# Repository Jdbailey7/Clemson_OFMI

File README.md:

# Clemson OFMI
This repository houses the hardware and software for the Optical Fiber Michelson
Interrogator (OFMI) designed for geophysical applications by Dr. Scott DeWolf.
Scott is an assistant research professor at Clemson University.

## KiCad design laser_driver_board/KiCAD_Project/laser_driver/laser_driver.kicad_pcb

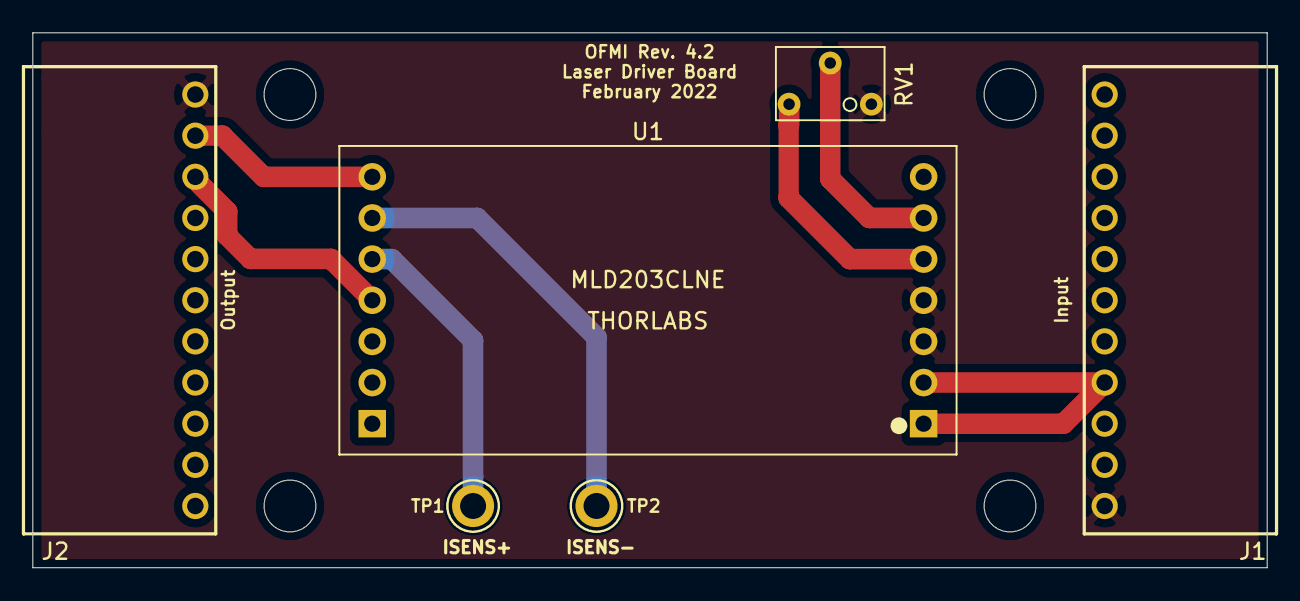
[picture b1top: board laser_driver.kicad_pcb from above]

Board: 2 copper layers, 76.2 x 33.0 mm, 11 parts (0 on the bottom side), 8 nets.

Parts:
H1, H2, H3, H4: MountingHole; MountingHole_3.2mm_M3_DIN965
J1: Input; SAMTEC-TSW-111-08-X-S-RA
J2: Output; SAMTEC-TSW-111-08-X-S-RA
PCB1: barepcb
RV1: 100k; 3266W
TP1, TP2: TestPoint; 5006_TestPoint
U1: MLD203CLNE; MLD203CLN

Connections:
+5V: J1.4, U1.1, U1.2
/ISENS+: TP1.1, U1.12
/ISENS-: TP2.1, U1.13
/ISET: RV1.2, U1.6
/LDA: J2.2, U1.14
/LDC: J2.3, U1.11
GND: J1.1, J2.1, RV1.1, U1.3, U1.4
unnamed: RV1.3, U1.5

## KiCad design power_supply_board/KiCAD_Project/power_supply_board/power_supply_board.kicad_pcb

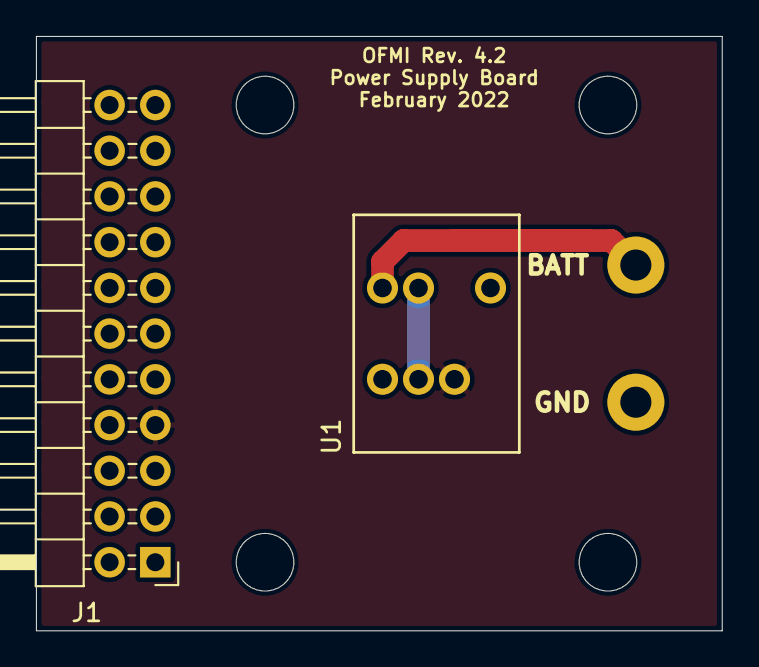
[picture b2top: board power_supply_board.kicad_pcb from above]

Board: 2 copper layers, 38.1 x 33.0 mm, 8 parts (0 on the bottom side), 3 nets.

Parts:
H1, H2, H3, H4: MountingHole; MountingHole_3.2mm_M3_DIN965
J1: To Digitiziers; Pin_Header_Angled_2x11_Pitch2.54mm
J2: Power Input; 16AWG
PCB1: barepcb
U1: TDN 5-2411WI; TDN5WI

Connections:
+5V: J1.7, U1.7
+BATT: J2.2, U1.1
GND: J1.1, J2.1, U1.2, U1.6

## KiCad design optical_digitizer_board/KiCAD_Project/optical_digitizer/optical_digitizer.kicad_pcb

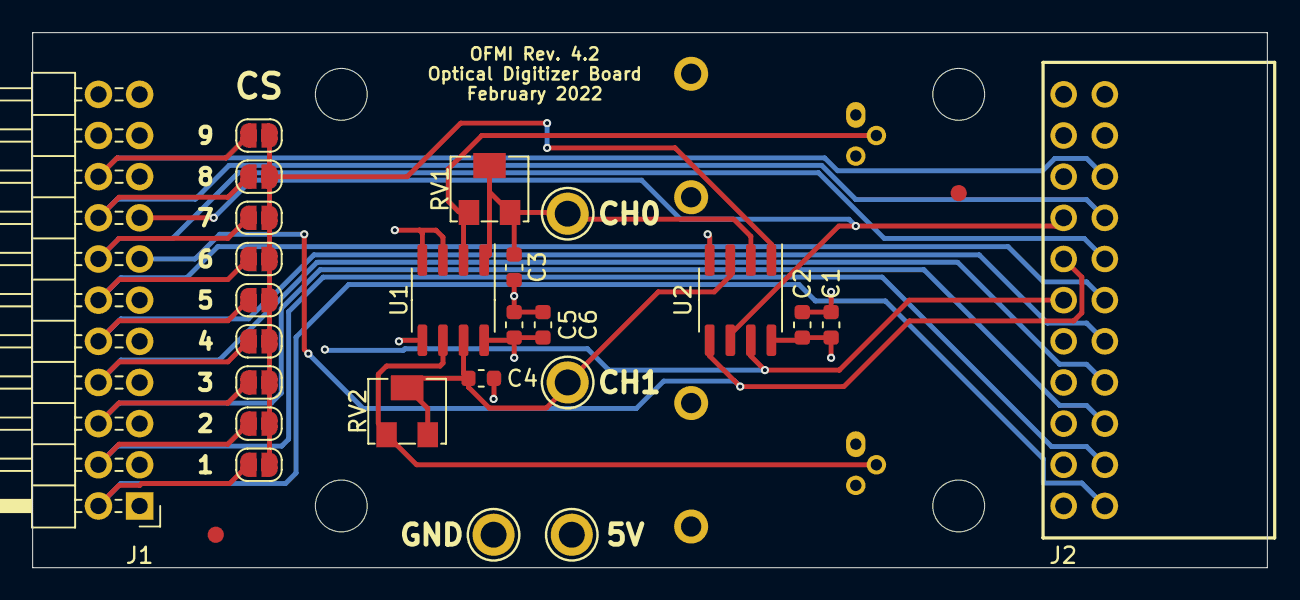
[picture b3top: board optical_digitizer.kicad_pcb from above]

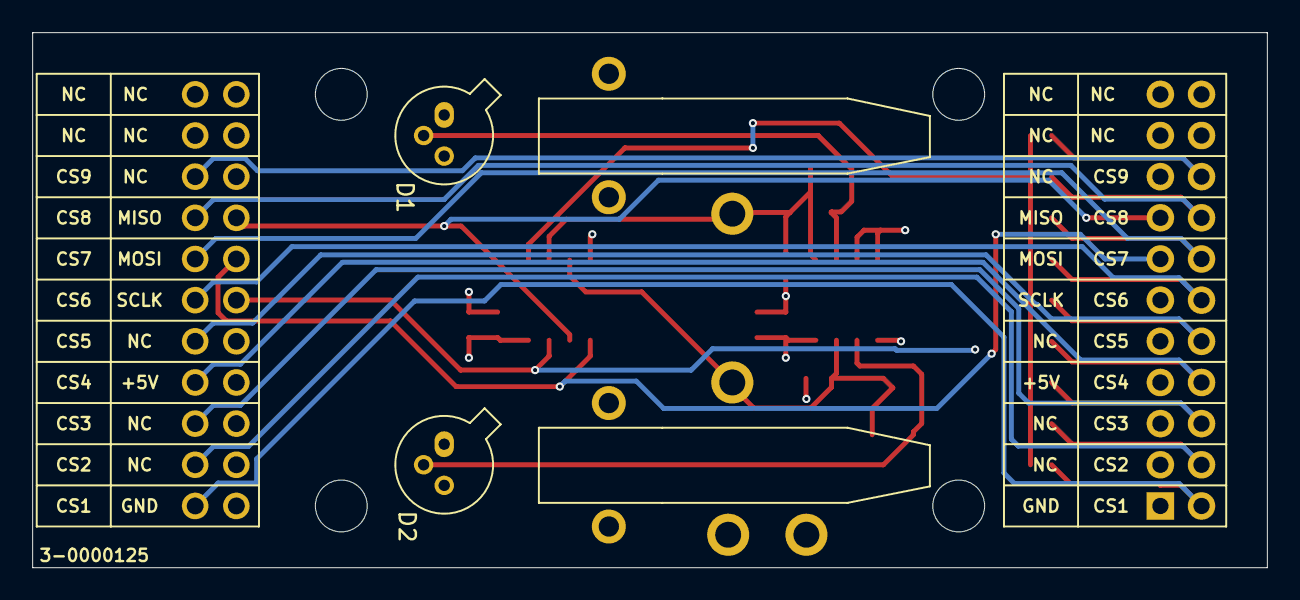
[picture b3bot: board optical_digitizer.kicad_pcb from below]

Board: 4 copper layers, 76.2 x 33.0 mm, 34 parts (2 on the bottom side), 19 nets.

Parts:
C1, C5: 1-0000007
C2, C6: 1-0000018
C3, C4: 1-0001030
D1, D2: PhotoDiode
FID1, FID2: Fiducial; Fiducial_1mm_Mask3mm
H1, H2, H3, H4: MountingHole; MountingHole_3.2mm_M3_DIN965
J1: Male Output Connector; Pin_Header_Angled_2x11_Pitch2.54mm
J2: Female Input Connector; SAMTEC-SSW-111-02-X-D-RA
JP1, JP2, JP3, JP4, JP5, JP6, JP7, JP8, JP9: Select CS; SolderJumper-2_P1.3mm_Open_RoundedPad1.0x1.5mm
PCB1: barepcb
RV1, RV2: 1-0001029
TP1, TP2, TP3, TP4: TestPoint; 5006_TestPoint
U1: 1-0001027
U2: 1-0001028

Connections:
+5V: C1.2, C2.2, C5.2, C6.2, J1.7, J2.7, TP3.1, U1.8, U2.8
/CS: JP1.1, JP2.1, JP3.1, JP4.1, JP5.1, JP6.1, JP7.1, JP8.1, JP9.1, U2.1
/CS1: J1.2, J2.2, JP1.2
/CS2: J1.4, J2.4, JP2.2
/CS3: J1.6, J2.6, JP3.2
/CS4: J1.8, J2.8, JP4.2
/CS5: J1.10, J2.10, JP5.2
/CS6: J1.12, J2.12, JP6.2
/CS7: J1.14, J2.14, JP7.2
/CS8: J1.16, J2.16, JP8.2
/CS9: J1.18, J2.18, JP9.2
/MISO: J1.15, J2.15, U2.6
/MOSI: J1.13, J2.13, U2.5
/SCLK: J1.11, J2.11, U2.7
GND: C1.1, C2.1, C3.2, C4.2, C5.1, C6.1, D1.1, D1.3, D1.4, D1.5, D2.1, D2.3, D2.4, D2.5, J1.1, J2.1, TP4.1, U1.3, U1.4, U1.5, U2.4
unnamed: C3.1, RV1.2, RV1.3, TP1.1, U1.1, U2.2
unnamed: C4.1, RV2.2, RV2.3, TP2.1, U1.7, U2.3
unnamed: D1.2, RV1.1, U1.2
unnamed: D2.2, RV2.1, U1.6

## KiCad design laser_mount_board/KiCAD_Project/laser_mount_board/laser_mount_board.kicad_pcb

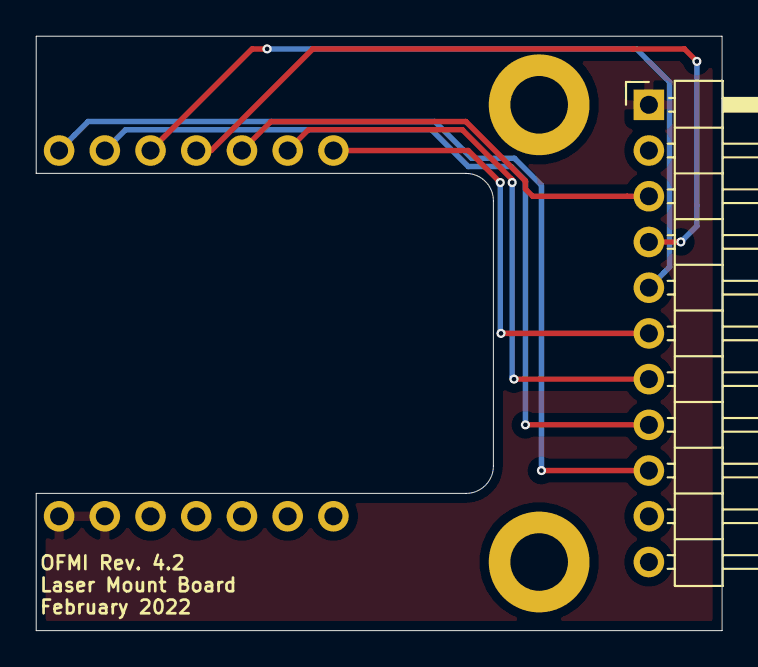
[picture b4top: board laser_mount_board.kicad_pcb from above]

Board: 2 copper layers, 38.1 x 33.0 mm, 5 parts (0 on the bottom side), 9 nets.

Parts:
H1, H2: M3; MountingHole_3.2mm_M3_DIN965_Pad
J1: Board to Board; Pin_Header_Angled_1x11_Pitch2.54mm
PCB1: barepcb
U1: LaserDiode

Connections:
GND: J1.1, U1.8, U1.9
LDA: J1.2, U1.11, U1.13
LDC: J1.3, U1.3
PDA: J1.4, U1.4
PDC: J1.5, U1.5
TEC+: J1.8, U1.6
TEC-: J1.9, U1.7
THERMA: J1.6, U1.1
THERMB: J1.7, U1.2

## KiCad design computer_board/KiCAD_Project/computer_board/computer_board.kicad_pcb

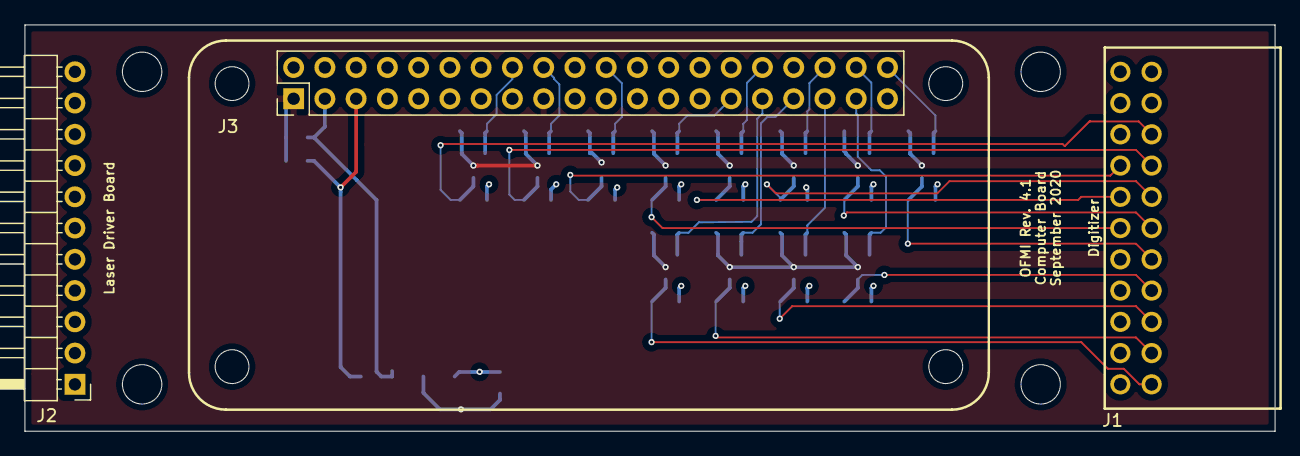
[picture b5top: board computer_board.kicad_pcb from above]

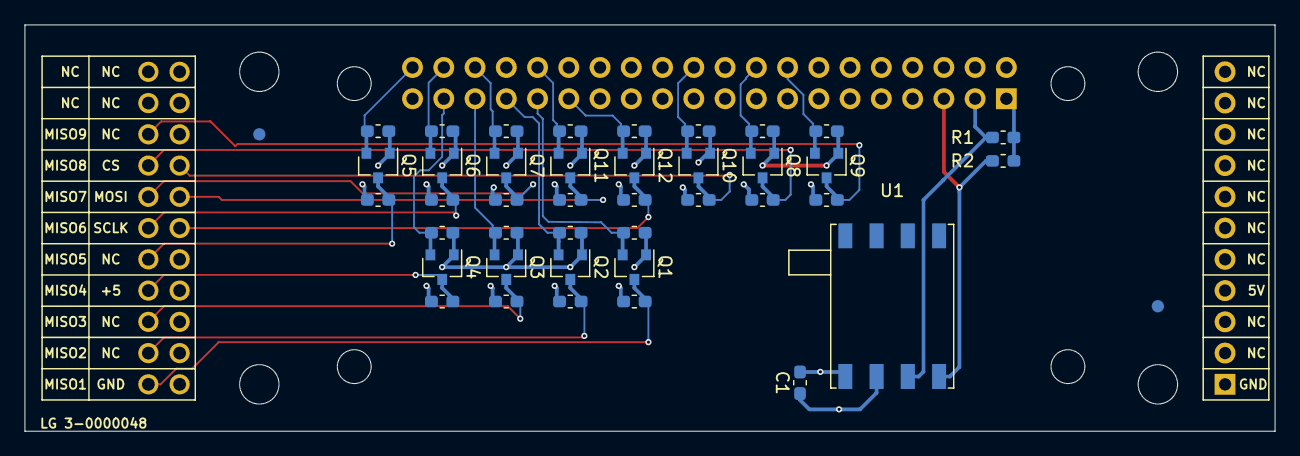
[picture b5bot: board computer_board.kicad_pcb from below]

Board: 4 copper layers, 101.6 x 33.0 mm, 49 parts (42 on the bottom side), 29 nets.

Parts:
C1: 0.1u; C_0603_1608Metric_Pad1.05x0.95mm_HandSolder
FID1, FID2: Fiducial; Fiducial_1mm_Mask3mm
H1, H2, H3, H4: MountingHole; MountingHole_3.2mm_M3_DIN965
J1: Digitiziers; SAMTEC-SSW-111-02-X-D-RA
J2: Laser Driver; Pin_Header_Angled_1x11_Pitch2.54mm
J3: Raspberry_Pi; Pi_Zero
Q1, Q2, Q3, Q4, Q5, Q6, Q7, Q8, Q9, Q10, Q11, Q12: BSS138; SOT-23
R1, R2: 1k; R_0603_1608Metric_Pad1.05x0.95mm_HandSolder
R3, R4, R5, R6, R7, R8, R9, R10, R11, R12, R13, R14, R15, R16, R17, R18, R19, R20, R21, R22, R23, R24, R25, R26: 10k; R_0603_1608Metric_Pad1.05x0.95mm_HandSolder
U1: SSCMRNN015PA3A3; SSCMRN

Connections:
+3V3: C1.1, J3.1, J3.17, Q1.1, Q2.1, Q3.1, Q4.1, Q5.1, Q6.1, Q7.1, Q8.1, Q9.1, Q10.1, Q11.1, Q12.1, R1.1, R2.1, R3.1, R4.1, R5.1, R6.1, R11.1, R12.1, R13.1, R14.1, R19.1, R20.1, R21.1, R22.1, U1.2
+5V: J1.7, J2.4, J3.2, J3.4, R7.1, R8.1, R9.1, R10.1, R15.1, R16.1, R17.1, R18.1, R23.1, R24.1, R25.1, R26.1
CS_3V3: J3.22, Q10.2, R20.2
CS_5V: J1.15, Q10.3, R24.2
GND: C1.2, J1.1, J2.1, J3.6, J3.9, J3.14, J3.20, J3.25, J3.30, J3.34, J3.39, U1.1
MISO1_3V3: J3.31, Q1.2, R3.2
MISO1_5V: J1.2, Q1.3, R7.2
MISO2_3V3: J3.33, Q2.2, R4.2
MISO2_5V: J1.4, Q2.3, R8.2
MISO3_3V3: J3.35, Q3.2, R5.2
MISO3_5V: J1.6, Q3.3, R9.2
MISO4_3V3: J3.37, Q4.2, R6.2
MISO4_5V: J1.8, Q4.3, R10.2
MISO5_3V3: J3.40, Q5.2, R11.2
MISO5_5V: J1.10, Q5.3, R15.2
MISO6_3V3: J3.38, Q6.2, R12.2
MISO6_5V: J1.12, Q6.3, R16.2
MISO7_3V3: J3.36, Q7.2, R13.2
MISO7_5V: J1.14, Q7.3, R17.2
MISO8_3V3: J3.18, Q8.2, R14.2
MISO8_5V: J1.16, Q8.3, R18.2
MISO9_3V3: J3.16, Q9.2, R19.2
MISO9_5V: J1.18, Q9.3, R23.2
MOSI_3V3: J3.32, Q11.2, R21.2
MOSI_5V: J1.13, Q11.3, R25.2
SCL: J3.5, R2.2, U1.4
SCLK_3V3: J3.29, Q12.2, R22.2
SCLK_5V: J1.11, Q12.3, R26.2
SDA: J3.3, R1.2, U1.3

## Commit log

2019-10-27 Initial draft of laser mount PCB.
2019-10-27 Update revision silkscreen text
2019-10-29 Laser mount board ready for review.
2019-10-29 Computer board ready for review.
2019-10-29 Laser driver board ready for review.
2019-10-29 Optical digitizer board ready for review.
2019-10-29 Power supply board ready for review.
2019-11-05 Add content to README
2019-11-05 Change computer board to OFMI
2019-11-05 Change laser driver to OFMI
2019-11-05 Change laser mount to OFMI
2019-11-05 Change optical digitizer to OFMI
2019-11-05 Change power supply to OFMI
2019-11-05 Standardize file names
2019-11-05 Track CSV
2019-11-05 Add BOMs
2020-01-01 Add Production ZIPs
2020-09-09 Minor design changes for Rev 4.1. Closes #4, #5, #6.
2020-09-09 Make changes for Rev 4.1
2020-09-09 Laser driver board rev 4.1 updates.
2020-09-09 Updates.
2020-09-09 Bump revisions to 4.1
2020-09-11 Finalize laser mount board.
2020-09-15 Finalize computer board
2020-09-15 finalize power supply board.
2020-09-15 Finalize optical digitizer
2020-09-15 Finalize laser driver board.
2020-09-15 Remove old inner layers from gerber output.
2021-02-13 Create PNP files.
2022-02-08 Update laser mount board to Rev 4.2. Closes #35
2022-02-08 Rev 4.2 of laser driver board. Closes #34
2022-02-08 Update power supply board to Rev 4.2. Closes #32.
2022-02-08 Revise optical digitizer to Rev 4.2
2022-02-08 Move pads apart for wire entry on power supply board
